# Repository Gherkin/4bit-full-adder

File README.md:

# 4bit-full-adder
discrete transistor CMOS NAND full adders

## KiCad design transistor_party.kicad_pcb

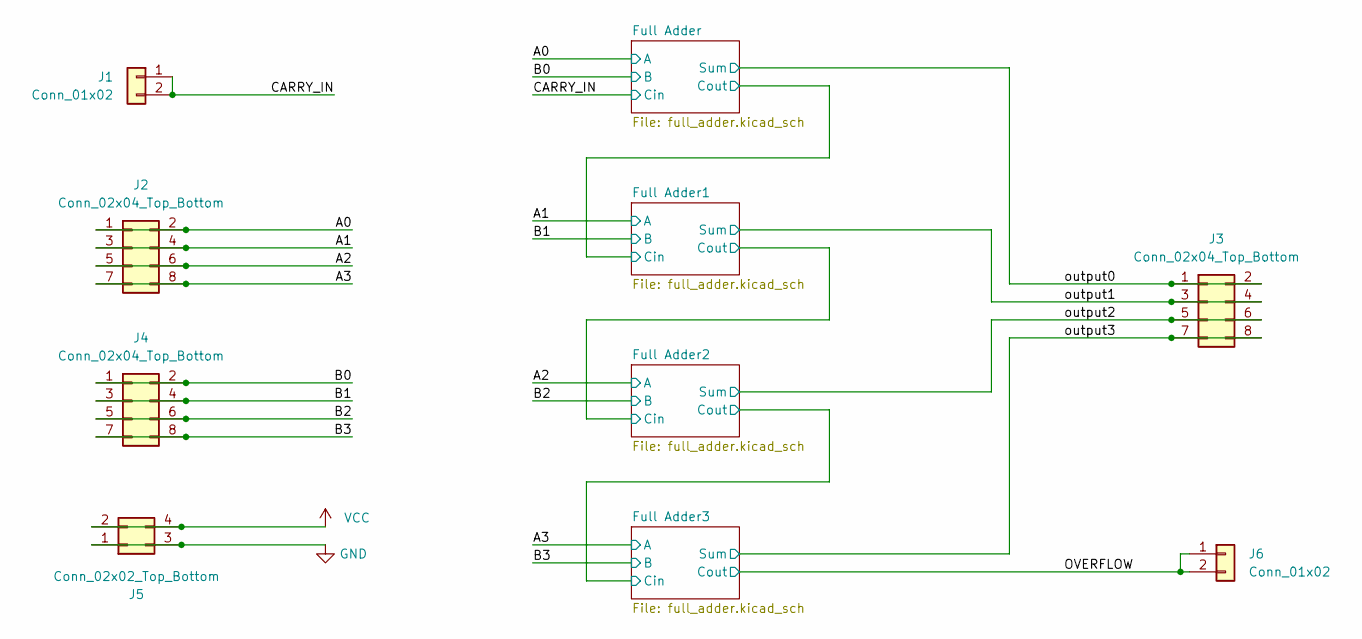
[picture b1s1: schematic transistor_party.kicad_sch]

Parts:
J1, J6: Conn_01x02; PinHeader_1x02_P2.54mm_Vertical
J2, J3, J4: Conn_02x04_Top_Bottom; PinHeader_2x04_P2.54mm_Vertical
J5: Conn_02x02_Top_Bottom; PinHeader_2x02_P2.54mm_Vertical

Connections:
/A0: J2.1, J2.2; also elsewhere on the board
/A1: J2.3, J2.4; also elsewhere on the board
/A2: J2.5, J2.6; also elsewhere on the board
/A3: J2.7, J2.8; also elsewhere on the board
/B0: J4.1, J4.2; also elsewhere on the board
/B1: J4.3, J4.4; also elsewhere on the board
/B2: J4.5, J4.6; also elsewhere on the board
/B3: J4.7, J4.8; also elsewhere on the board
/CARRY_IN: J1.1, J1.2; also elsewhere on the board
/OVERFLOW: J6.1, J6.2; also elsewhere on the board
/output0: J3.1, J3.2; also elsewhere on the board
/output1: J3.3, J3.4; also elsewhere on the board
/output2: J3.5, J3.6; also elsewhere on the board
/output3: J3.7, J3.8; also elsewhere on the board
GND: J5.1, J5.3; also elsewhere on the board
VCC: J5.2, J5.4; also elsewhere on the board

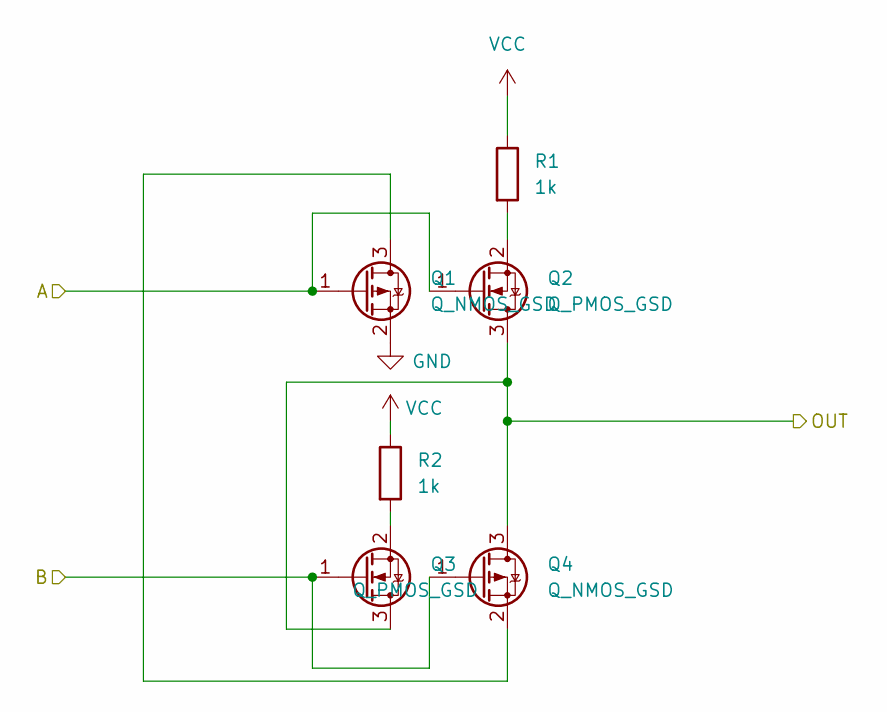
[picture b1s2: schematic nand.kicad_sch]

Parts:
Q1, Q4: Q_NMOS_GSD; SOT-23
Q2, Q3: Q_PMOS_GSD; SOT-23
R1, R2: 1k; R_0402_1005Metric

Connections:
/A0: Q1.1 (G), Q2.1 (G); also elsewhere on the board
/B0: Q3.1 (G), Q4.1 (G); also elsewhere on the board
/Full Adder/NAND1/OUT: Q2.3 (D), Q3.3 (D), Q4.3 (D); also elsewhere on the board
GND: Q1.2 (S); also elsewhere on the board
unnamed: Q1.3 (D), Q4.2 (S)
unnamed: Q2.2 (S), R1.2
unnamed: Q3.2 (S), R2.2
VCC: R1.1, R2.1; also elsewhere on the board

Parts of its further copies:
Q5, Q8, Q9, Q12, Q13, Q16, Q17, Q20, Q21, Q24, Q25, Q28, Q29, Q32, Q33, Q36, Q37, Q40, Q41, Q44, Q45, Q48, Q49, Q52, Q53, Q56, Q57, Q60, Q61, Q64, Q65, Q68, Q69, Q72, Q73, Q76, Q77, Q80, Q81, Q84, Q85, Q88, Q89, Q92, Q93, Q96, Q97, Q100, Q101, Q104, Q105, Q108, Q109, Q112, Q113, Q116, Q117, Q120, Q121, Q124, Q125, Q128, Q129, Q132, Q133, Q136, Q137, Q140, Q141, Q144: Q_NMOS_GSD; SOT-23
Q6, Q7, Q10, Q11, Q14, Q15, Q18, Q19, Q22, Q23, Q26, Q27, Q30, Q31, Q34, Q35, Q38, Q39, Q42, Q43, Q46, Q47, Q50, Q51, Q54, Q55, Q58, Q59, Q62, Q63, Q66, Q67, Q70, Q71, Q74, Q75, Q78, Q79, Q82, Q83, Q86, Q87, Q90, Q91, Q94, Q95, Q98, Q99, Q102, Q103, Q106, Q107, Q110, Q111, Q114, Q115, Q118, Q119, Q122, Q123, Q126, Q127, Q130, Q131, Q134, Q135, Q138, Q139, Q142, Q143: Q_PMOS_GSD; SOT-23
R3, R4, R5, R6, R7, R8, R9, R10, R11, R12, R13, R14, R15, R16, R17, R18, R19, R20, R21, R22, R23, R24, R25, R26, R27, R28, R29, R30, R31, R32, R33, R34, R35, R36, R37, R38, R39, R40, R41, R42, R43, R44, R45, R46, R47, R48, R49, R50, R51, R52, R53, R54, R55, R56, R57, R58, R59, R60, R61, R62, R63, R64, R65, R66, R67, R68, R69, R70, R71, R72: 1k; R_0402_1005Metric

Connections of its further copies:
/A0: Q5.1 (G), Q6.1 (G); also elsewhere on the board
/A1: Q37.1 (G), Q38.1 (G), Q45.1 (G), Q46.1 (G); also elsewhere on the board
/A2: Q73.1 (G), Q74.1 (G), Q81.1 (G), Q82.1 (G); also elsewhere on the board
/A3: Q109.1 (G), Q110.1 (G), Q117.1 (G), Q118.1 (G); also elsewhere on the board
/B0: Q11.1 (G), Q12.1 (G); also elsewhere on the board
/B1: Q39.1 (G), Q40.1 (G), Q43.1 (G), Q44.1 (G); also elsewhere on the board
/B2: Q75.1 (G), Q76.1 (G), Q79.1 (G), Q80.1 (G); also elsewhere on the board
/B3: Q111.1 (G), Q112.1 (G), Q115.1 (G), Q116.1 (G); also elsewhere on the board
/CARRY_IN: Q19.1 (G), Q20.1 (G), Q27.1 (G), Q28.1 (G); also elsewhere on the board
/Full Adder1/Cout: Q66.3 (D), Q67.3 (D), Q68.3 (D), Q91.1 (G), Q92.1 (G), Q99.1 (G), Q100.1 (G)
/Full Adder1/NAND1/OUT: Q38.3 (D), Q39.3 (D), Q40.3 (D), Q41.1 (G), Q42.1 (G), Q47.1 (G), Q48.1 (G), Q67.1 (G), Q68.1 (G)
/Full Adder1/NAND2/OUT: Q46.3 (D), Q47.3 (D), Q48.3 (D), Q49.1 (G), Q50.1 (G)
/Full Adder1/NAND3/OUT: Q42.3 (D), Q43.3 (D), Q44.3 (D), Q51.1 (G), Q52.1 (G)
/Full Adder1/NAND4/OUT: Q50.3 (D), Q51.3 (D), Q52.3 (D), Q53.1 (G), Q54.1 (G), Q57.1 (G), Q58.1 (G)
/Full Adder1/NAND5/OUT: Q54.3 (D), Q55.3 (D), Q56.3 (D), Q59.1 (G), Q60.1 (G), Q61.1 (G), Q62.1 (G), Q65.1 (G), Q66.1 (G)
/Full Adder1/NAND6/OUT: Q58.3 (D), Q59.3 (D), Q60.3 (D), Q69.1 (G), Q70.1 (G)
/Full Adder1/NAND7/OUT: Q62.3 (D), Q63.3 (D), Q64.3 (D), Q71.1 (G), Q72.1 (G)
/Full Adder2/Cout: Q102.3 (D), Q103.3 (D), Q104.3 (D), Q127.1 (G), Q128.1 (G), Q135.1 (G), Q136.1 (G)
/Full Adder2/NAND1/OUT: Q74.3 (D), Q75.3 (D), Q76.3 (D), Q77.1 (G), Q78.1 (G), Q83.1 (G), Q84.1 (G), Q103.1 (G), Q104.1 (G)
/Full Adder2/NAND2/OUT: Q82.3 (D), Q83.3 (D), Q84.3 (D), Q85.1 (G), Q86.1 (G)
/Full Adder2/NAND3/OUT: Q78.3 (D), Q79.3 (D), Q80.3 (D), Q87.1 (G), Q88.1 (G)
/Full Adder2/NAND4/OUT: Q86.3 (D), Q87.3 (D), Q88.3 (D), Q89.1 (G), Q90.1 (G), Q93.1 (G), Q94.1 (G)
/Full Adder2/NAND5/OUT: Q90.3 (D), Q91.3 (D), Q92.3 (D), Q95.1 (G), Q96.1 (G), Q97.1 (G), Q98.1 (G), Q101.1 (G), Q102.1 (G)
/Full Adder2/NAND6/OUT: Q94.3 (D), Q95.3 (D), Q96.3 (D), Q105.1 (G), Q106.1 (G)
/Full Adder2/NAND7/OUT: Q98.3 (D), Q99.3 (D), Q100.3 (D), Q107.1 (G), Q108.1 (G)
/Full Adder3/NAND1/OUT: Q110.3 (D), Q111.3 (D), Q112.3 (D), Q113.1 (G), Q114.1 (G), Q119.1 (G), Q120.1 (G), Q139.1 (G), Q140.1 (G)
/Full Adder3/NAND2/OUT: Q118.3 (D), Q119.3 (D), Q120.3 (D), Q121.1 (G), Q122.1 (G)
/Full Adder3/NAND3/OUT: Q114.3 (D), Q115.3 (D), Q116.3 (D), Q123.1 (G), Q124.1 (G)
/Full Adder3/NAND4/OUT: Q122.3 (D), Q123.3 (D), Q124.3 (D), Q125.1 (G), Q126.1 (G), Q129.1 (G), Q130.1 (G)
/Full Adder3/NAND5/OUT: Q126.3 (D), Q127.3 (D), Q128.3 (D), Q131.1 (G), Q132.1 (G), Q133.1 (G), Q134.1 (G), Q137.1 (G), Q138.1 (G)
/Full Adder3/NAND6/OUT: Q130.3 (D), Q131.3 (D), Q132.3 (D), Q141.1 (G), Q142.1 (G)
/Full Adder3/NAND7/OUT: Q134.3 (D), Q135.3 (D), Q136.3 (D), Q143.1 (G), Q144.1 (G)
/Full Adder/Cout: Q34.3 (D), Q35.3 (D), Q36.3 (D), Q55.1 (G), Q56.1 (G), Q63.1 (G), Q64.1 (G)
/Full Adder/NAND1/OUT: Q7.1 (G), Q8.1 (G), Q9.1 (G), Q10.1 (G), Q35.1 (G), Q36.1 (G); also elsewhere on the board
/Full Adder/NAND2/OUT: Q6.3 (D), Q7.3 (D), Q8.3 (D), Q13.1 (G), Q14.1 (G)
/Full Adder/NAND3/OUT: Q10.3 (D), Q11.3 (D), Q12.3 (D), Q15.1 (G), Q16.1 (G)
/Full Adder/NAND4/OUT: Q14.3 (D), Q15.3 (D), Q16.3 (D), Q17.1 (G), Q18.1 (G), Q21.1 (G), Q22.1 (G)
/Full Adder/NAND5/OUT: Q18.3 (D), Q19.3 (D), Q20.3 (D), Q23.1 (G), Q24.1 (G), Q25.1 (G), Q26.1 (G), Q33.1 (G), Q34.1 (G)
/Full Adder/NAND6/OUT: Q22.3 (D), Q23.3 (D), Q24.3 (D), Q29.1 (G), Q30.1 (G)
/Full Adder/NAND7/OUT: Q26.3 (D), Q27.3 (D), Q28.3 (D), Q31.1 (G), Q32.1 (G)
/OVERFLOW: Q138.3 (D), Q139.3 (D), Q140.3 (D); also elsewhere on the board
/output0: Q30.3 (D), Q31.3 (D), Q32.3 (D); also elsewhere on the board
/output1: Q70.3 (D), Q71.3 (D), Q72.3 (D); also elsewhere on the board
/output2: Q106.3 (D), Q107.3 (D), Q108.3 (D); also elsewhere on the board
/output3: Q142.3 (D), Q143.3 (D), Q144.3 (D); also elsewhere on the board
GND: Q5.2 (S), Q9.2 (S), Q13.2 (S), Q17.2 (S), Q21.2 (S), Q25.2 (S), Q29.2 (S), Q33.2 (S), Q37.2 (S), Q41.2 (S), Q45.2 (S), Q49.2 (S), Q53.2 (S), Q57.2 (S), Q61.2 (S), Q65.2 (S), Q69.2 (S), Q73.2 (S), Q77.2 (S), Q81.2 (S), Q85.2 (S), Q89.2 (S), Q93.2 (S), Q97.2 (S), Q101.2 (S), Q105.2 (S), Q109.2 (S), Q113.2 (S), Q117.2 (S), Q121.2 (S), Q125.2 (S), Q129.2 (S), Q133.2 (S), Q137.2 (S), Q141.2 (S); also elsewhere on the board
unnamed: Q5.3 (D), Q8.2 (S)
unnamed: Q6.2 (S), R3.2
unnamed: Q7.2 (S), R4.2
unnamed: Q10.2 (S), R5.2
unnamed: Q11.2 (S), R6.2
unnamed: Q9.3 (D), Q12.2 (S)
unnamed: Q13.3 (D), Q16.2 (S)
unnamed: Q14.2 (S), R7.2
unnamed: Q15.2 (S), R8.2
unnamed: Q17.3 (D), Q20.2 (S)
unnamed: Q18.2 (S), R9.2
unnamed: Q19.2 (S), R10.2
unnamed: Q21.3 (D), Q24.2 (S)
unnamed: Q22.2 (S), R11.2
unnamed: Q23.2 (S), R12.2
unnamed: Q25.3 (D), Q28.2 (S)
unnamed: Q26.2 (S), R13.2
unnamed: Q27.2 (S), R14.2
unnamed: Q29.3 (D), Q32.2 (S)
unnamed: Q30.2 (S), R15.2
unnamed: Q31.2 (S), R16.2
unnamed: Q33.3 (D), Q36.2 (S)
unnamed: Q34.2 (S), R17.2
unnamed: Q35.2 (S), R18.2
unnamed: Q37.3 (D), Q40.2 (S)
unnamed: Q38.2 (S), R19.2
unnamed: Q39.2 (S), R20.2
unnamed: Q41.3 (D), Q44.2 (S)
unnamed: Q42.2 (S), R21.2
unnamed: Q43.2 (S), R22.2
unnamed: Q45.3 (D), Q48.2 (S)
unnamed: Q46.2 (S), R23.2
unnamed: Q47.2 (S), R24.2
unnamed: Q49.3 (D), Q52.2 (S)
unnamed: Q50.2 (S), R25.2
unnamed: Q51.2 (S), R26.2
unnamed: Q53.3 (D), Q56.2 (S)
unnamed: Q54.2 (S), R27.2
unnamed: Q55.2 (S), R28.2
unnamed: Q57.3 (D), Q60.2 (S)
unnamed: Q58.2 (S), R29.2
unnamed: Q59.2 (S), R30.2
unnamed: Q61.3 (D), Q64.2 (S)
unnamed: Q62.2 (S), R31.2
unnamed: Q63.2 (S), R32.2
unnamed: Q65.3 (D), Q68.2 (S)
unnamed: Q66.2 (S), R33.2
unnamed: Q67.2 (S), R34.2
unnamed: Q69.3 (D), Q72.2 (S)
unnamed: Q70.2 (S), R35.2
unnamed: Q71.2 (S), R36.2
unnamed: Q73.3 (D), Q76.2 (S)
unnamed: Q74.2 (S), R37.2
unnamed: Q75.2 (S), R38.2
unnamed: Q77.3 (D), Q80.2 (S)
unnamed: Q78.2 (S), R39.2
unnamed: Q79.2 (S), R40.2
unnamed: Q81.3 (D), Q84.2 (S)
unnamed: Q82.2 (S), R41.2
unnamed: Q83.2 (S), R42.2
unnamed: Q85.3 (D), Q88.2 (S)
unnamed: Q86.2 (S), R43.2
unnamed: Q87.2 (S), R44.2
unnamed: Q89.3 (D), Q92.2 (S)
unnamed: Q90.2 (S), R45.2
unnamed: Q91.2 (S), R46.2
unnamed: Q93.3 (D), Q96.2 (S)
unnamed: Q94.2 (S), R47.2
unnamed: Q95.2 (S), R48.2
unnamed: Q98.2 (S), R49.2
unnamed: Q99.2 (S), R50.2
unnamed: Q97.3 (D), Q100.2 (S)
unnamed: Q101.3 (D), Q104.2 (S)
unnamed: Q102.2 (S), R51.2
unnamed: Q103.2 (S), R52.2
unnamed: Q105.3 (D), Q108.2 (S)
unnamed: Q106.2 (S), R53.2
unnamed: Q107.2 (S), R54.2
unnamed: Q109.3 (D), Q112.2 (S)
unnamed: Q110.2 (S), R55.2
unnamed: Q111.2 (S), R56.2
unnamed: Q113.3 (D), Q116.2 (S)
unnamed: Q114.2 (S), R57.2
unnamed: Q115.2 (S), R58.2
unnamed: Q117.3 (D), Q120.2 (S)
unnamed: Q118.2 (S), R59.2
unnamed: Q119.2 (S), R60.2
unnamed: Q121.3 (D), Q124.2 (S)
unnamed: Q122.2 (S), R61.2
unnamed: Q123.2 (S), R62.2
unnamed: Q125.3 (D), Q128.2 (S)
unnamed: Q126.2 (S), R63.2
unnamed: Q127.2 (S), R64.2
unnamed: Q129.3 (D), Q132.2 (S)
unnamed: Q130.2 (S), R65.2
unnamed: Q131.2 (S), R66.2
unnamed: Q133.3 (D), Q136.2 (S)
unnamed: Q134.2 (S), R67.2
unnamed: Q135.2 (S), R68.2
unnamed: Q137.3 (D), Q140.2 (S)
unnamed: Q138.2 (S), R69.2
unnamed: Q139.2 (S), R70.2
unnamed: Q141.3 (D), Q144.2 (S)
unnamed: Q142.2 (S), R71.2
unnamed: Q143.2 (S), R72.2
VCC: R3.1, R4.1, R5.1, R6.1, R7.1, R8.1, R9.1, R10.1, R11.1, R12.1, R13.1, R14.1, R15.1, R16.1, R17.1, R18.1, R19.1, R20.1, R21.1, R22.1, R23.1, R24.1, R25.1, R26.1, R27.1, R28.1, R29.1, R30.1, R31.1, R32.1, R33.1, R34.1, R35.1, R36.1, R37.1, R38.1, R39.1, R40.1, R41.1, R42.1, R43.1, R44.1, R45.1, R46.1, R47.1, R48.1, R49.1, R50.1, R51.1, R52.1, R53.1, R54.1, R55.1, R56.1, R57.1, R58.1, R59.1, R60.1, R61.1, R62.1, R63.1, R64.1, R65.1, R66.1, R67.1, R68.1, R69.1, R70.1, R71.1, R72.1; also elsewhere on the board

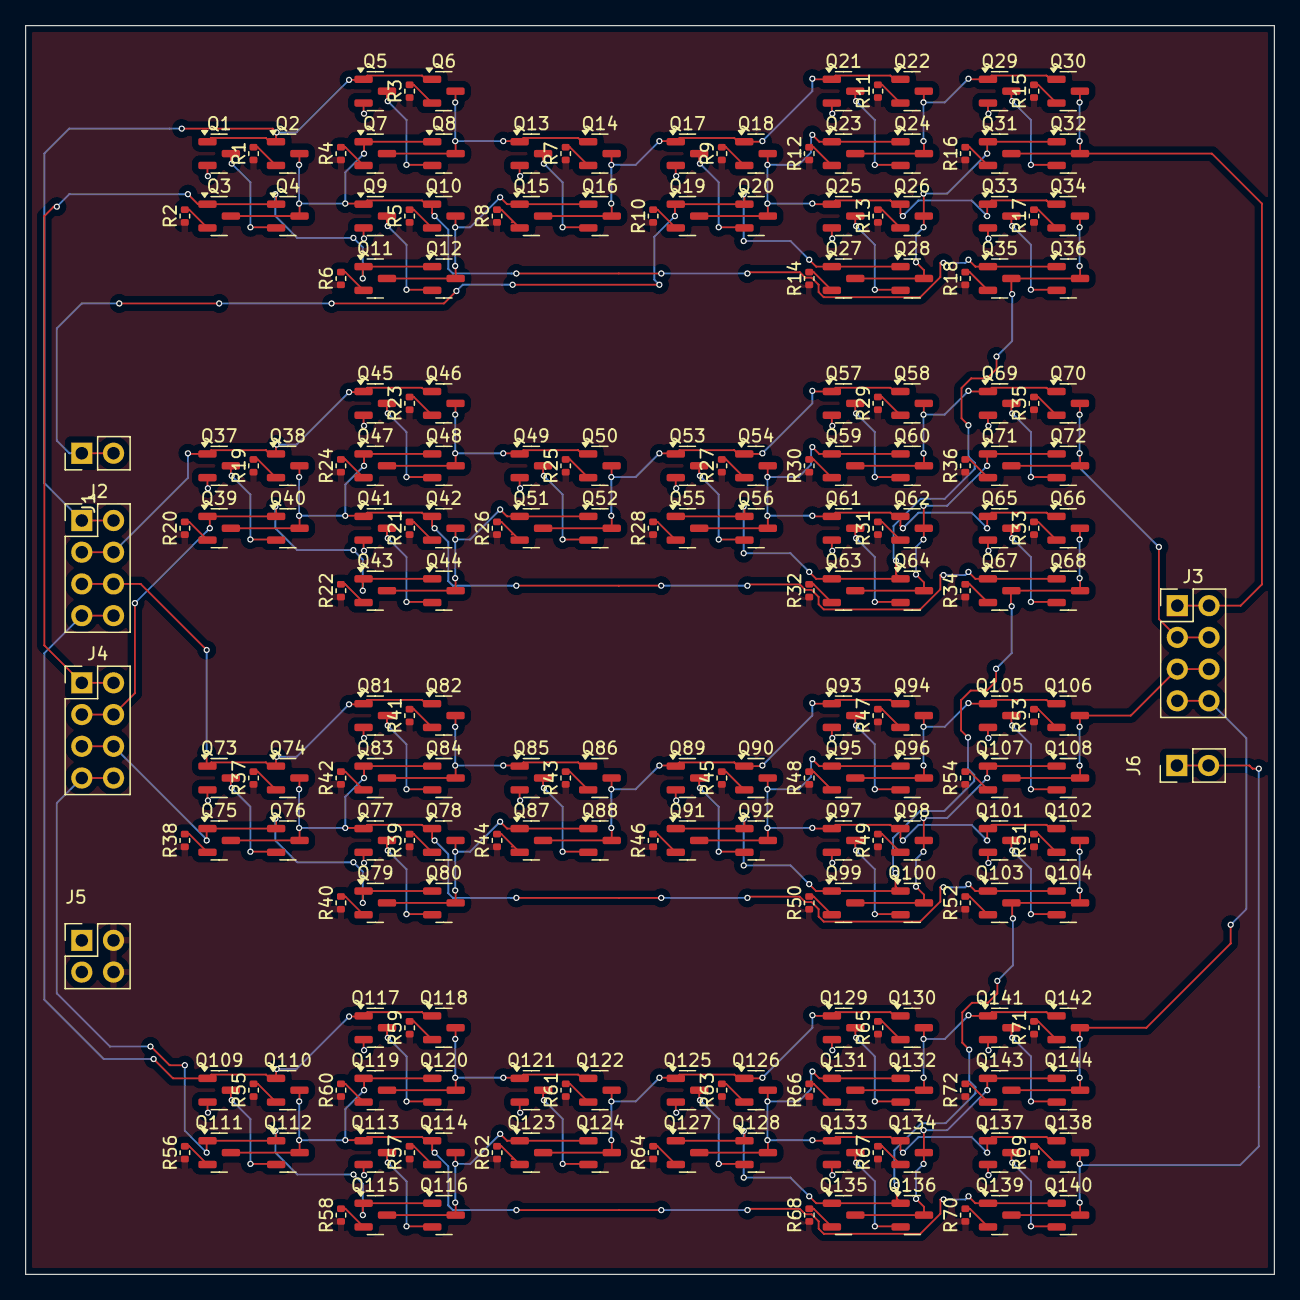
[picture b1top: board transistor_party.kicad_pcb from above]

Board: 2 copper layers, 100.0 x 100.0 mm, 222 parts (0 on the bottom side), 155 nets.

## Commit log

2024-05-22 init
2024-05-22 changed readme
